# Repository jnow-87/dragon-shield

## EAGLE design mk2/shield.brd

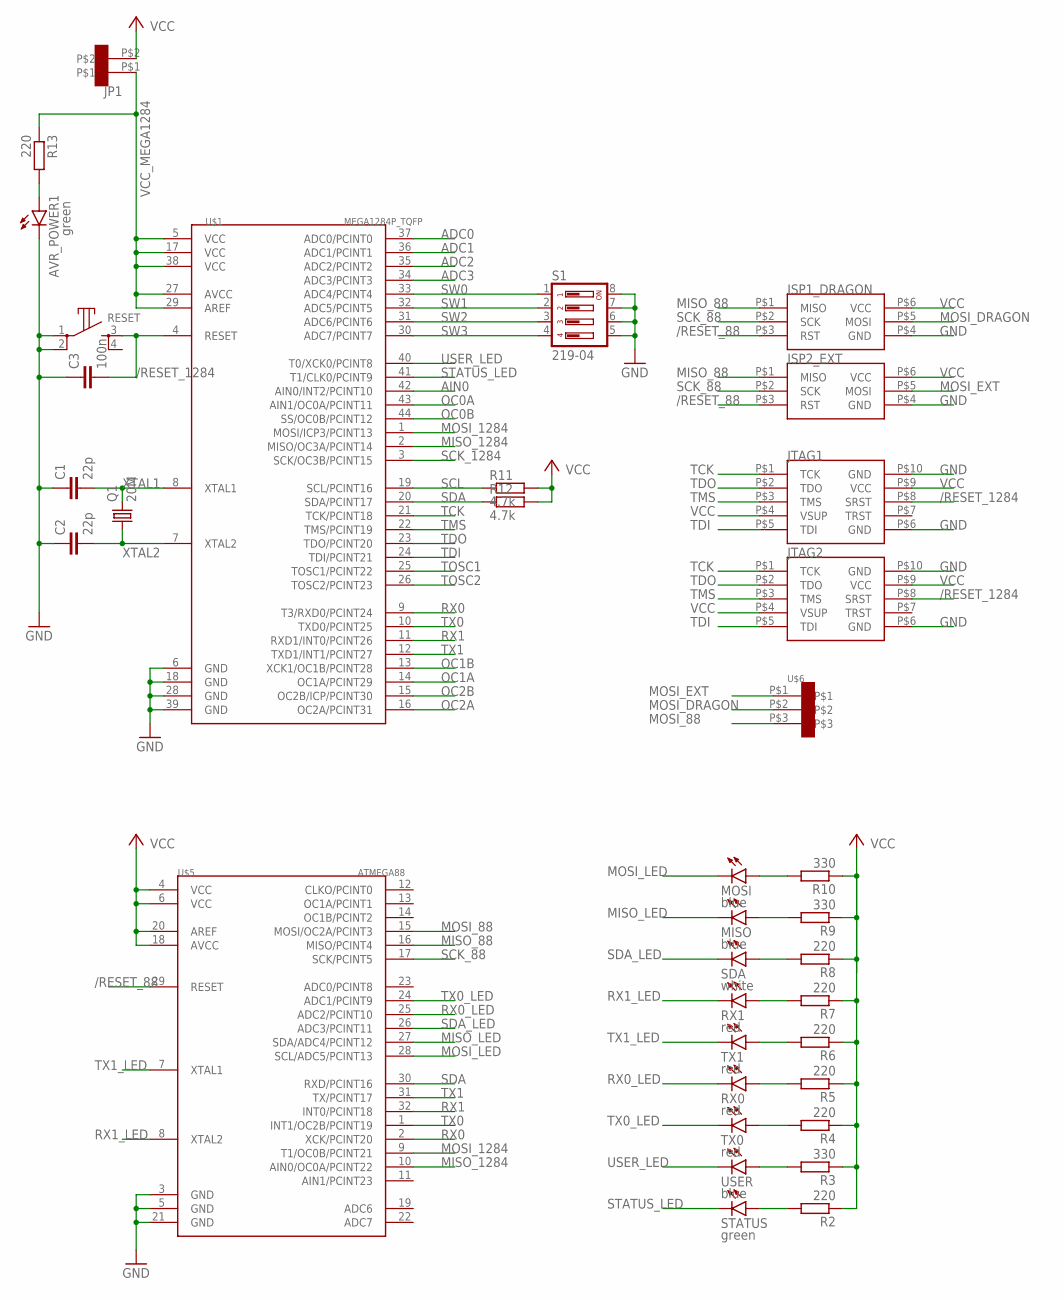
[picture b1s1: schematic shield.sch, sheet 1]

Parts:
AVR_POWER1: green; CHIP-LED0603
C1, C2: 22p; C0603
C3: 100n; C0603
ISP1_DRAGON, ISP2_EXT: ISP; CON_DIL_2X3
JP1: CON_DIL_2
JTAG1, JTAG2: JTAG; CON_DIL_2X5
MISO: blue; CHIP-LED0603
MOSI: blue; CHIP-LED0603
Q1: 20M; HC49U-V
R2, R4, R5, R6, R7, R8, R13: 220; R0603
R3, R9, R10: 330; R0603
R11, R12: 4.7k; R0603
RESET: 4-1437565-2; B3S-10XX
RX0, RX1: red; CHIP-LED0603
S1: 219-04; CTS-219-04
SDA: white; CHIP-LED0603
STATUS: green; CHIP-LED0603
TX0, TX1: red; CHIP-LED0603
U$1: MEGA1284P_TQFP; TQFP44
U$5: ATMEGA88; TQFP32-08
U$6: CON_DIL_3
USER: blue; CHIP-LED0603

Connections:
/RESET_88: ISP1_DRAGON.P$3 (RST), ISP2_EXT.P$3 (RST), U$5.29 (RESET)
/RESET_1284: C3.2, JTAG1.P$8 (SRST), JTAG2.P$8 (SRST), RESET.3, U$1.4 (RESET); also elsewhere on the board
ADC0: U$1.37 (ADC0/PCINT0); also elsewhere on the board
ADC1: U$1.36 (ADC1/PCINT1); also elsewhere on the board
ADC2: U$1.35 (ADC2/PCINT2); also elsewhere on the board
ADC3: U$1.34 (ADC3/PCINT3); also elsewhere on the board
AIN0: U$1.42 (AIN0/INT2/PCINT10); also elsewhere on the board
GND: AVR_POWER1.C, C1.1, C2.1, C3.1, ISP1_DRAGON.P$4 (GND), ISP2_EXT.P$4 (GND), JTAG1.P$6 (GND), JTAG1.P$10 (GND), JTAG2.P$6 (GND), JTAG2.P$10 (GND), RESET.1, RESET.2, S1.5, S1.6, S1.7, S1.8, U$1.6 (GND), U$1.18 (GND), U$1.28 (GND), U$1.39 (GND), U$5.3 (GND), U$5.5 (GND), U$5.21 (GND); also elsewhere on the board
MISO_88: ISP1_DRAGON.P$1 (MISO), ISP2_EXT.P$1 (MISO), U$5.16 (MISO/PCINT4)
MISO_1284: U$1.2 (MISO/OC3A/PCINT14), U$5.10 (AIN0/OC0A/PCINT22); also elsewhere on the board
MISO_LED: MISO.C, U$5.27 (SDA/ADC4/PCINT12)
MOSI_88: U$5.15 (MOSI/OC2A/PCINT3), U$6.P$3
MOSI_1284: U$1.1 (MOSI/ICP3/PCINT13), U$5.9 (T1/OC0B/PCINT21); also elsewhere on the board
MOSI_DRAGON: ISP1_DRAGON.P$5 (MOSI), U$6.P$2
MOSI_EXT: ISP2_EXT.P$5 (MOSI), U$6.P$1
MOSI_LED: MOSI.C, U$5.28 (SCL/ADC5/PCINT13)
unnamed: R2.2, STATUS.A
unnamed: R4.2, TX0.A
unnamed: R5.2, RX0.A
unnamed: R6.2, TX1.A
unnamed: R7.2, RX1.A
unnamed: R8.2, SDA.A
unnamed: R3.2, USER.A
unnamed: MISO.A, R9.2
unnamed: MOSI.A, R10.2
unnamed: AVR_POWER1.A, R13.2
OC0A: U$1.43 (AIN1/OC0A/PCINT11); also elsewhere on the board
OC0B: U$1.44 (SS/OC0B/PCINT12); also elsewhere on the board
OC1A: U$1.14 (OC1A/PCINT29); also elsewhere on the board
OC1B: U$1.13 (XCK1/OC1B/PCINT28); also elsewhere on the board
OC2A: U$1.16 (OC2A/PCINT31); also elsewhere on the board
OC2B: U$1.15 (OC2B/ICP/PCINT30); also elsewhere on the board
RX0: U$1.9 (T3/RXD0/PCINT24), U$5.2 (XCK/PCINT20); also elsewhere on the board
RX0_LED: RX0.C, U$5.25 (ADC2/PCINT10)
RX1: U$1.11 (RXD1/INT0/PCINT26), U$5.32 (INT0/PCINT18); also elsewhere on the board
RX1_LED: RX1.C, U$5.8 (XTAL2)
SCK_88: ISP1_DRAGON.P$2 (SCK), ISP2_EXT.P$2 (SCK), U$5.17 (SCK/PCINT5)
SCK_1284: U$1.3 (SCK/OC3B/PCINT15); also elsewhere on the board
SCL: R11.1, U$1.19 (SCL/PCINT16); also elsewhere on the board
SDA: R12.1, U$1.20 (SDA/PCINT17), U$5.30 (RXD/PCINT16); also elsewhere on the board
SDA_LED: SDA.C, U$5.26 (ADC3/PCINT11)
STATUS_LED: STATUS.C, U$1.41 (T1/CLK0/PCINT9); also elsewhere on the board
SW0: S1.1, U$1.33 (ADC4/PCINT4); also elsewhere on the board
SW1: S1.2, U$1.32 (ADC5/PCINT5); also elsewhere on the board
SW2: S1.3, U$1.31 (ADC6/PCINT6); also elsewhere on the board
SW3: S1.4, U$1.30 (ADC7/PCINT7); also elsewhere on the board
TCK: JTAG1.P$1 (TCK), JTAG2.P$1 (TCK), U$1.21 (TCK/PCINT18); also elsewhere on the board
TDI: JTAG1.P$5 (TDI), JTAG2.P$5 (TDI), U$1.24 (TDI/PCINT21); also elsewhere on the board
TDO: JTAG1.P$2 (TDO), JTAG2.P$2 (TDO), U$1.23 (TDO/PCINT20); also elsewhere on the board
TMS: JTAG1.P$3 (TMS), JTAG2.P$3 (TMS), U$1.22 (TMS/PCINT19); also elsewhere on the board
TOSC1: U$1.25 (TOSC1/PCINT22); also elsewhere on the board
TOSC2: U$1.26 (TOSC2/PCINT23); also elsewhere on the board
TX0: U$1.10 (TXD0/PCINT25), U$5.1 (INT1/OC2B/PCINT19); also elsewhere on the board
TX0_LED: TX0.C, U$5.24 (ADC1/PCINT9)
TX1: U$1.12 (TXD1/INT1/PCINT27), U$5.31 (TX/PCINT17); also elsewhere on the board
TX1_LED: TX1.C, U$5.7 (XTAL1)
USER_LED: U$1.40 (T0/XCK0/PCINT8), USER.C; also elsewhere on the board
VCC: ISP1_DRAGON.P$6 (VCC), ISP2_EXT.P$6 (VCC), JP1.P$2, JTAG1.P$4 (VSUP), JTAG1.P$9 (VCC), JTAG2.P$4 (VSUP), JTAG2.P$9 (VCC), R2.1, R3.1, R4.1, R5.1, R6.1, R7.1, R8.1, R9.1, R10.1, R11.2, R12.2, U$5.4 (VCC), U$5.6 (VCC), U$5.18 (AVCC), U$5.20 (AREF); also elsewhere on the board
VCC_MEGA1284: JP1.P$1, R13.1, U$1.5 (VCC), U$1.17 (VCC), U$1.27 (AVCC), U$1.29 (AREF), U$1.38 (VCC); also elsewhere on the board
XTAL1: C1.2, Q1.2, U$1.8 (XTAL1); also elsewhere on the board
XTAL2: C2.2, Q1.1, U$1.7 (XTAL2); also elsewhere on the board

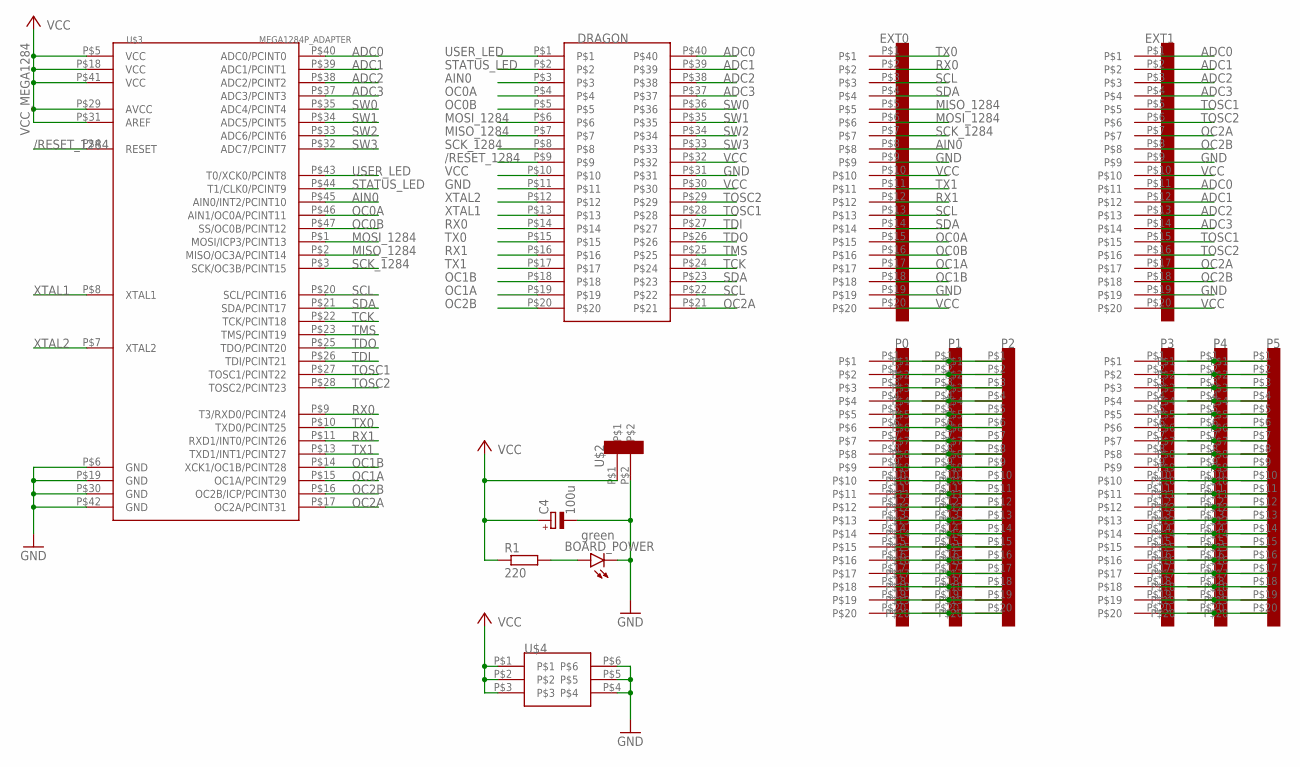
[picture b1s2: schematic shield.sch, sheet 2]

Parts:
BOARD_POWER: green; CHIP-LED0603
C4: 100u; E2,5-5
DRAGON: CON_DIL_2X20
EXT0, EXT1: CON_DIL_20
P0, P1, P2, P3, P4, P5: CON_DIL_20
R1: 220; R0603
U$2: CON_DIL_2
U$3: MEGA1284P_ADAPTER; TQFP44-ADAPTER
U$4: CON_DIL_2X3

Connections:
/RESET_1284: DRAGON.P$9, U$3.P$4 (RESET); also elsewhere on the board
ADC0: DRAGON.P$40, EXT1.P$1, EXT1.P$11, U$3.P$40 (ADC0/PCINT0); also elsewhere on the board
ADC1: DRAGON.P$39, EXT1.P$2, EXT1.P$12, U$3.P$39 (ADC1/PCINT1); also elsewhere on the board
ADC2: DRAGON.P$38, EXT1.P$3, EXT1.P$13, U$3.P$38 (ADC2/PCINT2); also elsewhere on the board
ADC3: DRAGON.P$37, EXT1.P$4, EXT1.P$14, U$3.P$37 (ADC3/PCINT3); also elsewhere on the board
AIN0: DRAGON.P$3, EXT0.P$8, U$3.P$45 (AIN0/INT2/PCINT10); also elsewhere on the board
GND: BOARD_POWER.C, C4.-, DRAGON.P$11, DRAGON.P$31, EXT0.P$9, EXT0.P$19, EXT1.P$9, EXT1.P$19, U$2.P$2, U$3.P$6 (GND), U$3.P$19 (GND), U$3.P$30 (GND), U$3.P$42 (GND), U$4.P$4, U$4.P$5, U$4.P$6; also elsewhere on the board
MISO_1284: DRAGON.P$7, EXT0.P$5, U$3.P$2 (MISO/OC3A/PCINT14); also elsewhere on the board
MOSI_1284: DRAGON.P$6, EXT0.P$6, U$3.P$1 (MOSI/ICP3/PCINT13); also elsewhere on the board
unnamed: BOARD_POWER.A, R1.2
unnamed: P0.P$1, P1.P$1, P2.P$1
unnamed: P0.P$2, P1.P$2, P2.P$2
unnamed: P0.P$3, P1.P$3, P2.P$3
unnamed: P0.P$4, P1.P$4, P2.P$4
unnamed: P0.P$5, P1.P$5, P2.P$5
unnamed: P0.P$6, P1.P$6, P2.P$6
unnamed: P0.P$7, P1.P$7, P2.P$7
unnamed: P0.P$8, P1.P$8, P2.P$8
unnamed: P0.P$9, P1.P$9, P2.P$9
unnamed: P0.P$10, P1.P$10, P2.P$10
unnamed: P0.P$11, P1.P$11, P2.P$11
unnamed: P0.P$12, P1.P$12, P2.P$12
unnamed: P0.P$13, P1.P$13, P2.P$13
unnamed: P0.P$14, P1.P$14, P2.P$14
unnamed: P0.P$15, P1.P$15, P2.P$15
unnamed: P0.P$16, P1.P$16, P2.P$16
unnamed: P0.P$17, P1.P$17, P2.P$17
unnamed: P0.P$18, P1.P$18, P2.P$18
unnamed: P0.P$19, P1.P$19, P2.P$19
unnamed: P0.P$20, P1.P$20, P2.P$20
unnamed: P3.P$1, P4.P$1, P5.P$1
unnamed: P3.P$2, P4.P$2, P5.P$2
unnamed: P3.P$3, P4.P$3, P5.P$3
unnamed: P3.P$4, P4.P$4, P5.P$4
unnamed: P3.P$5, P4.P$5, P5.P$5
unnamed: P3.P$6, P4.P$6, P5.P$6
unnamed: P3.P$7, P4.P$7, P5.P$7
unnamed: P3.P$8, P4.P$8, P5.P$8
unnamed: P3.P$9, P4.P$9, P5.P$9
unnamed: P3.P$10, P4.P$10, P5.P$10
unnamed: P3.P$11, P4.P$11, P5.P$11
unnamed: P3.P$12, P4.P$12, P5.P$12
unnamed: P3.P$13, P4.P$13, P5.P$13
unnamed: P3.P$14, P4.P$14, P5.P$14
unnamed: P3.P$15, P4.P$15, P5.P$15
unnamed: P3.P$16, P4.P$16, P5.P$16
unnamed: P3.P$17, P4.P$17, P5.P$17
unnamed: P3.P$18, P4.P$18, P5.P$18
unnamed: P3.P$19, P4.P$19, P5.P$19
unnamed: P3.P$20, P4.P$20, P5.P$20
OC0A: DRAGON.P$4, EXT0.P$15, U$3.P$46 (AIN1/OC0A/PCINT11); also elsewhere on the board
OC0B: DRAGON.P$5, EXT0.P$16, U$3.P$47 (SS/OC0B/PCINT12); also elsewhere on the board
OC1A: DRAGON.P$19, EXT0.P$17, U$3.P$15 (OC1A/PCINT29); also elsewhere on the board
OC1B: DRAGON.P$18, EXT0.P$18, U$3.P$14 (XCK1/OC1B/PCINT28); also elsewhere on the board
OC2A: DRAGON.P$21, EXT1.P$7, EXT1.P$17, U$3.P$17 (OC2A/PCINT31); also elsewhere on the board
OC2B: DRAGON.P$20, EXT1.P$8, EXT1.P$18, U$3.P$16 (OC2B/ICP/PCINT30); also elsewhere on the board
RX0: DRAGON.P$14, EXT0.P$2, U$3.P$9 (T3/RXD0/PCINT24); also elsewhere on the board
RX1: DRAGON.P$16, EXT0.P$12, U$3.P$11 (RXD1/INT0/PCINT26); also elsewhere on the board
SCK_1284: DRAGON.P$8, EXT0.P$7, U$3.P$3 (SCK/OC3B/PCINT15); also elsewhere on the board
SCL: DRAGON.P$22, EXT0.P$3, EXT0.P$13, U$3.P$20 (SCL/PCINT16); also elsewhere on the board
SDA: DRAGON.P$23, EXT0.P$4, EXT0.P$14, U$3.P$21 (SDA/PCINT17); also elsewhere on the board
STATUS_LED: DRAGON.P$2, U$3.P$44 (T1/CLK0/PCINT9); also elsewhere on the board
SW0: DRAGON.P$36, U$3.P$35 (ADC4/PCINT4); also elsewhere on the board
SW1: DRAGON.P$35, U$3.P$34 (ADC5/PCINT5); also elsewhere on the board
SW2: DRAGON.P$34, U$3.P$33 (ADC6/PCINT6); also elsewhere on the board
SW3: DRAGON.P$33, U$3.P$32 (ADC7/PCINT7); also elsewhere on the board
TCK: DRAGON.P$24, U$3.P$22 (TCK/PCINT18); also elsewhere on the board
TDI: DRAGON.P$27, U$3.P$26 (TDI/PCINT21); also elsewhere on the board
TDO: DRAGON.P$26, U$3.P$25 (TDO/PCINT20); also elsewhere on the board
TMS: DRAGON.P$25, U$3.P$23 (TMS/PCINT19); also elsewhere on the board
TOSC1: DRAGON.P$28, EXT1.P$5, EXT1.P$15, U$3.P$27 (TOSC1/PCINT22); also elsewhere on the board
TOSC2: DRAGON.P$29, EXT1.P$6, EXT1.P$16, U$3.P$28 (TOSC2/PCINT23); also elsewhere on the board
TX0: DRAGON.P$15, EXT0.P$1, U$3.P$10 (TXD0/PCINT25); also elsewhere on the board
TX1: DRAGON.P$17, EXT0.P$11, U$3.P$13 (TXD1/INT1/PCINT27); also elsewhere on the board
USER_LED: DRAGON.P$1, U$3.P$43 (T0/XCK0/PCINT8); also elsewhere on the board
VCC: C4.+, DRAGON.P$10, DRAGON.P$30, DRAGON.P$32, EXT0.P$10, EXT0.P$20, EXT1.P$10, EXT1.P$20, R1.1, U$2.P$1, U$4.P$1, U$4.P$2, U$4.P$3; also elsewhere on the board
VCC_MEGA1284: U$3.P$5 (VCC), U$3.P$18 (VCC), U$3.P$29 (AVCC), U$3.P$31 (AREF), U$3.P$41 (VCC); also elsewhere on the board
XTAL1: DRAGON.P$13, U$3.P$8 (XTAL1); also elsewhere on the board
XTAL2: DRAGON.P$12, U$3.P$7 (XTAL2); also elsewhere on the board

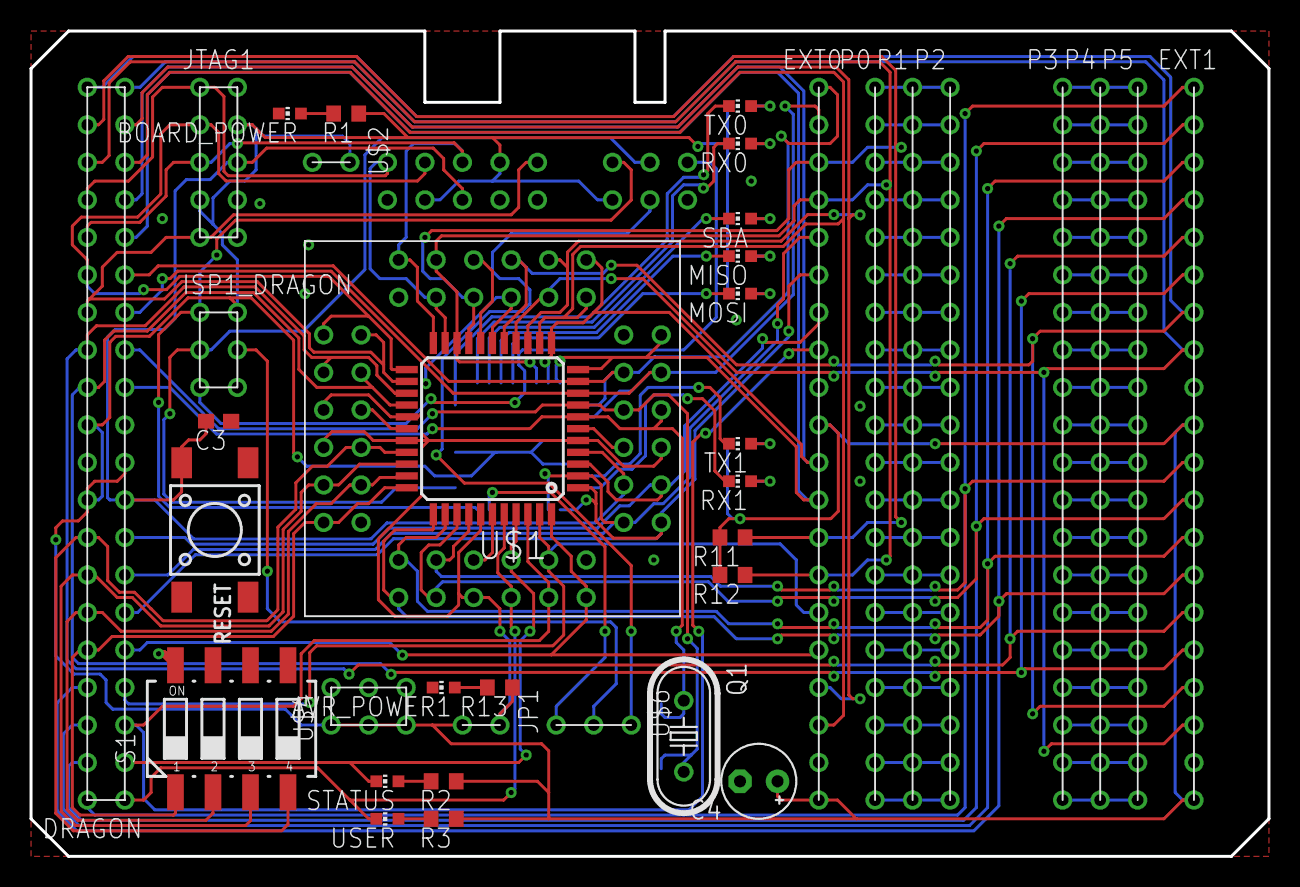
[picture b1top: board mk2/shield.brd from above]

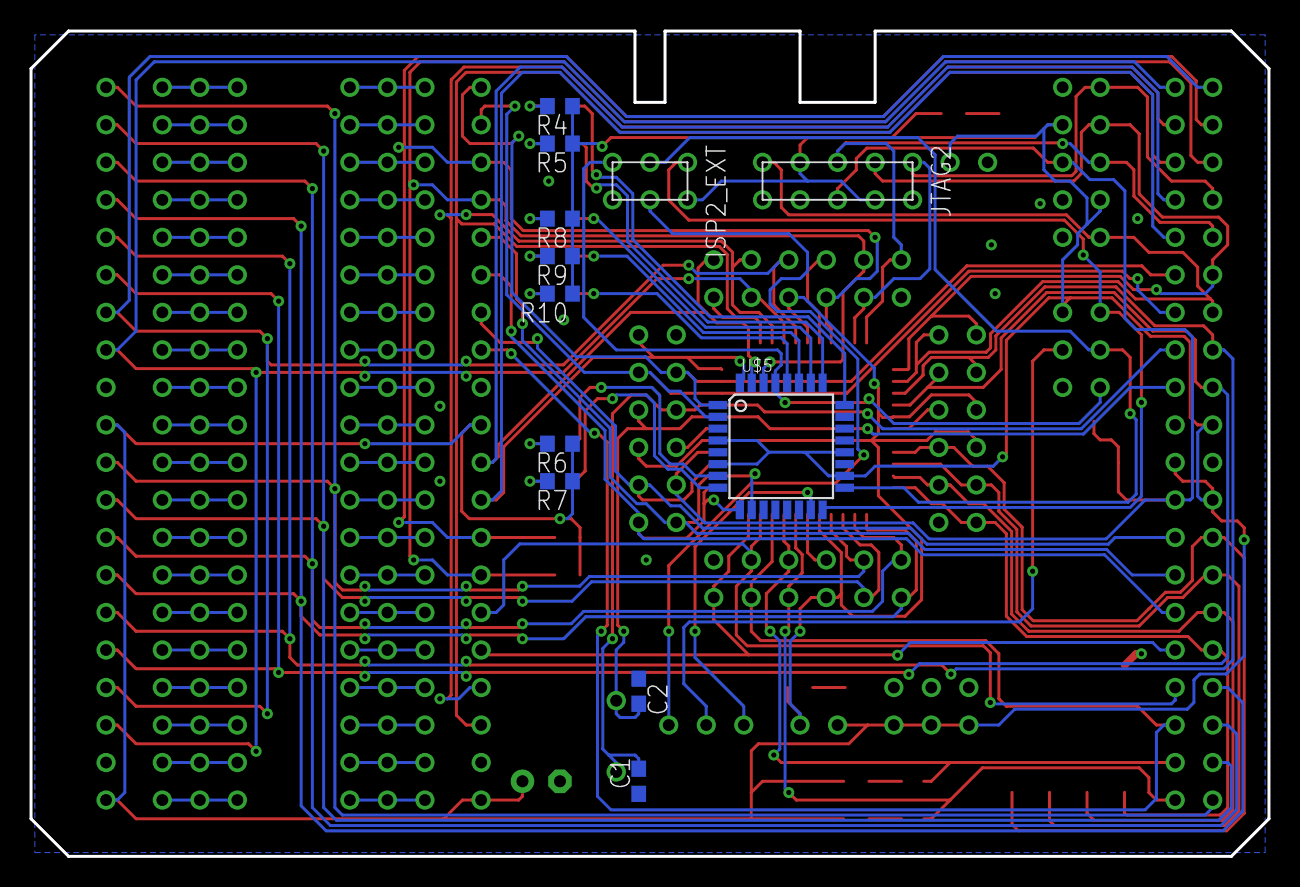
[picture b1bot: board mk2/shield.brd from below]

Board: 2 copper layers, 83.8 x 55.9 mm, 51 parts (12 on the bottom side), 102 nets.

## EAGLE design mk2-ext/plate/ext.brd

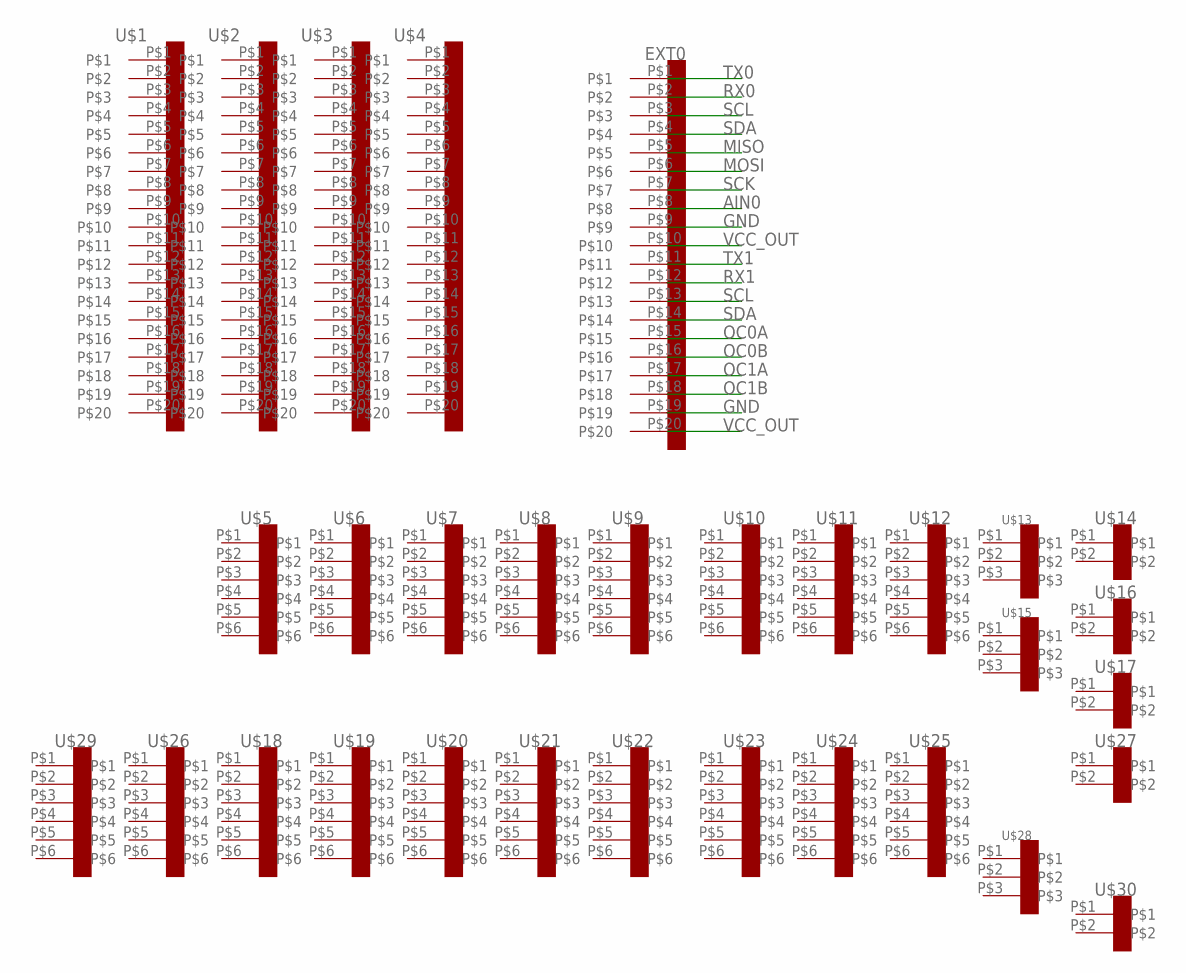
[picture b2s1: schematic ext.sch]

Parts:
EXT0: CON_DIL_20
U$1, U$2, U$3, U$4: CON_DIL_20
U$5, U$6, U$7, U$8, U$9, U$10, U$11, U$12, U$18, U$19, U$20, U$21, U$22, U$23, U$24, U$25, U$26, U$29: CON_DIL_6
U$13, U$15, U$28: CON_DIL_3
U$14, U$16, U$17, U$27, U$30: CON_DIL_2

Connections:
AIN0: EXT0.P$8
GND: EXT0.P$9, EXT0.P$19
MISO: EXT0.P$5
MOSI: EXT0.P$6
OC0A: EXT0.P$15
OC0B: EXT0.P$16
OC1A: EXT0.P$17
OC1B: EXT0.P$18
RX0: EXT0.P$2
RX1: EXT0.P$12
SCK: EXT0.P$7
SCL: EXT0.P$3, EXT0.P$13
SDA: EXT0.P$4, EXT0.P$14
TX0: EXT0.P$1
TX1: EXT0.P$11
VCC_OUT: EXT0.P$10, EXT0.P$20

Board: 2 copper layers, 31 parts (0 on the bottom side), 4 nets, no tracks yet.

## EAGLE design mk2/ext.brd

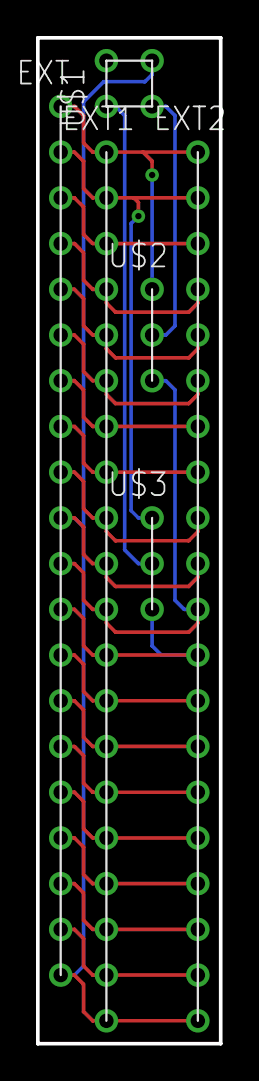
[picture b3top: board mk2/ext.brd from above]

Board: 2 copper layers, 10.2 x 55.9 mm, 6 parts (0 on the bottom side), 20 nets.

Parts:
EXT, EXT1, EXT2: CON_DIL_20
U$1: CON_DIL_2X2
U$2, U$3: CON_DIL_3

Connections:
EXT_AIN0: EXT.P$8, EXT1.P$8, EXT2.P$8
EXT_MISO: EXT.P$5, EXT1.P$5, EXT2.P$5
EXT_MOSI: EXT.P$6, EXT1.P$6, EXT2.P$6
EXT_OC0A: EXT.P$15, EXT1.P$15, EXT2.P$15
EXT_OC0B: EXT.P$16, EXT1.P$16, EXT2.P$16
EXT_OC1A: EXT.P$17, EXT1.P$17, EXT2.P$17
EXT_OC1B: EXT.P$18, EXT1.P$18, EXT2.P$18
EXT_RX0: EXT.P$2, EXT1.P$2, EXT2.P$2, U$3.P$1
EXT_RX1: EXT.P$12, EXT1.P$12, EXT2.P$12, U$3.P$3
EXT_SCK: EXT.P$7, EXT1.P$7, EXT2.P$7
EXT_SCL0: EXT.P$3, EXT1.P$3, EXT2.P$3
EXT_SCL1: EXT.P$13, EXT1.P$13, EXT2.P$13
EXT_SDA0: EXT.P$4, EXT1.P$4, EXT2.P$4
EXT_SDA1: EXT.P$14, EXT1.P$14, EXT2.P$14
EXT_TX0: EXT.P$1, EXT1.P$1, EXT2.P$1, U$2.P$1
EXT_TX1: EXT.P$11, EXT1.P$11, EXT2.P$11, U$2.P$3
GND: EXT.P$9, EXT.P$19, EXT1.P$9, EXT1.P$19, EXT2.P$9, EXT2.P$19, U$1.P$3
RX: U$1.P$1, U$3.P$2
TX: U$1.P$2, U$2.P$2
VCC: EXT.P$10, EXT.P$20, EXT1.P$10, EXT1.P$20, EXT2.P$10, EXT2.P$20, U$1.P$4

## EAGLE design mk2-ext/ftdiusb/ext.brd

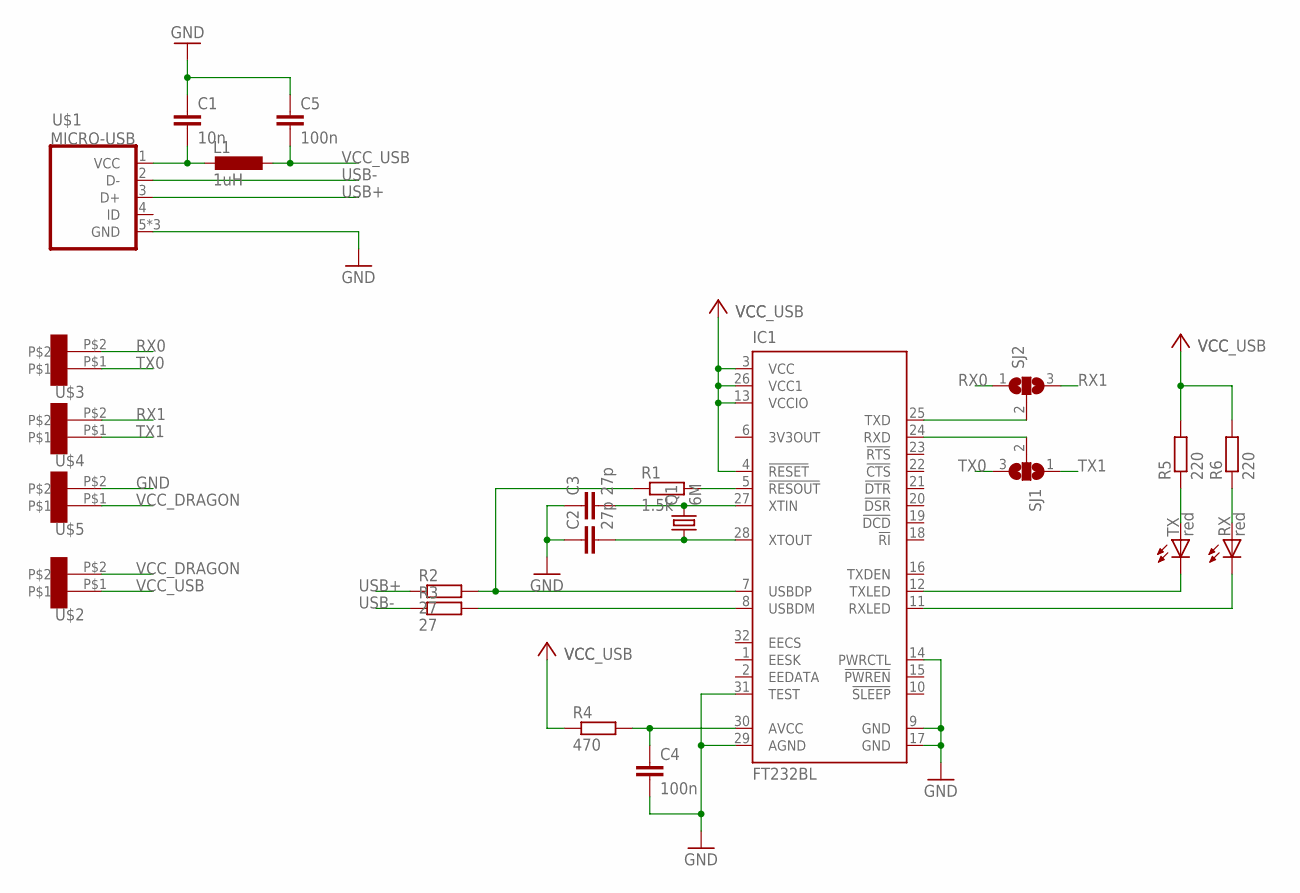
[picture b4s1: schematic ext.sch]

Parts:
C1: 10n; C0603
C2, C3: 27p; C0603
C4, C5: 100n; C0603
IC1: FT232BL; LQFP32-7X7
L1: 1uH; L0603
Q1: 6M; HC49U-V
R1: 1.5k; R0603
R2, R3: 27; R0603
R4: 470; R0603
R5, R6: 220; R0603
RX: red; C0603
SJ1, SJ2: SJ2WW; SJ_2W
TX: red; C0603
U$1: MICRO-USB
U$2, U$3, U$4, U$5: CON_DIL_2

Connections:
GND: C1.1, C2.1, C3.1, C4.2, C5.1, IC1.9 (GND), IC1.14 (PWRCTL), IC1.17 (GND), IC1.29 (AGND), IC1.31 (TEST), U$1.5 (GND), U$1.GND1 (GND), U$1.GND2 (GND), U$5.P$2
unnamed: IC1.5 (!RESOUT), R1.2
unnamed: IC1.7 (USBDP), R1.1, R2.2
unnamed: IC1.8 (USBDM), R3.2
unnamed: C1.2, L1.2, U$1.1 (VCC)
unnamed: IC1.25 (TXD), SJ2.2
unnamed: C3.2, IC1.27 (XTIN), Q1.2
unnamed: C2.2, IC1.28 (XTOUT), Q1.1
unnamed: IC1.24 (RXD), SJ1.2
unnamed: IC1.12 (TXLED), TX.N
unnamed: R5.1, TX.P
unnamed: C4.1, IC1.30 (AVCC), R4.2
unnamed: R6.1, RX.P
unnamed: IC1.11 (RXLED), RX.N
RX0: SJ2.1, U$3.P$2
RX1: SJ2.3, U$4.P$2
TX0: SJ1.3, U$3.P$1
TX1: SJ1.1, U$4.P$1
USB+: R2.1, U$1.3 (D+)
USB-: R3.1, U$1.2 (D-)
VCC_DRAGON: U$2.P$2, U$5.P$1
VCC_USB: C5.2, IC1.3 (VCC), IC1.4 (!RESET), IC1.13 (VCCIO), IC1.26 (VCC1), L1.1, R4.1, R5.2, R6.2, U$2.P$1

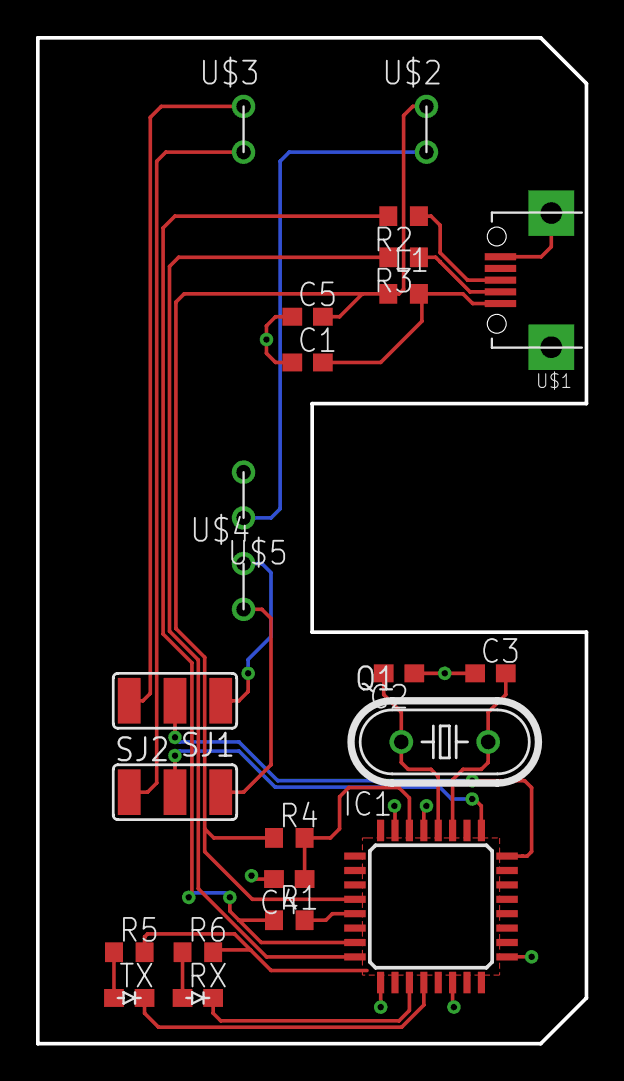
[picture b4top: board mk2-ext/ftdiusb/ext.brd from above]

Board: 2 copper layers, 30.5 x 55.9 mm, 23 parts (0 on the bottom side), 22 nets.

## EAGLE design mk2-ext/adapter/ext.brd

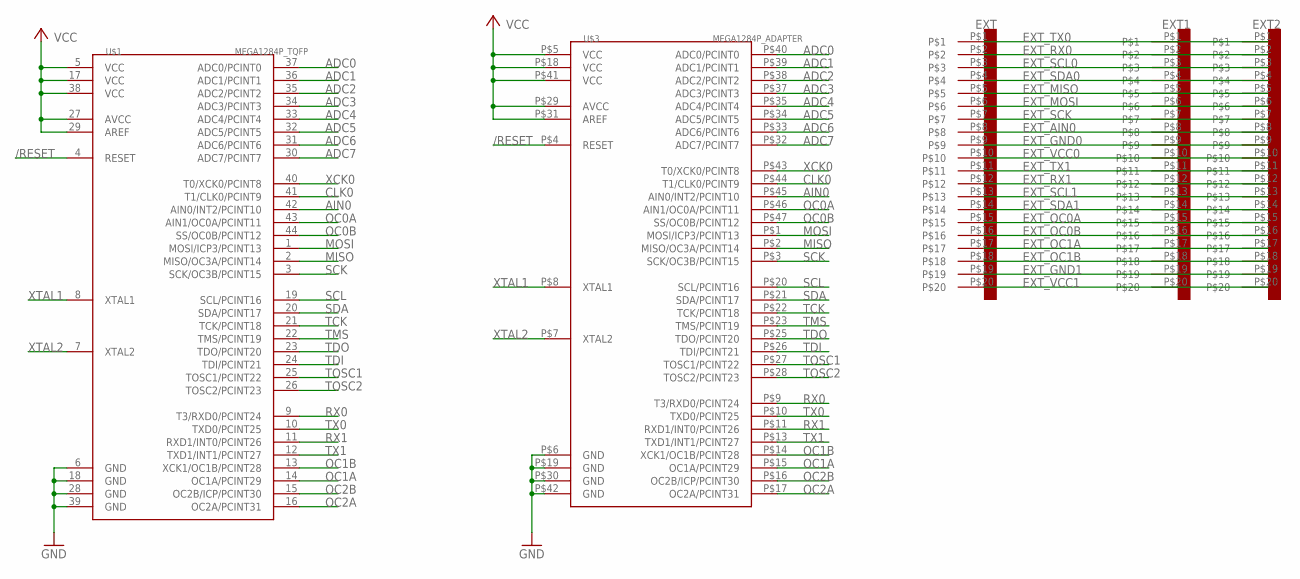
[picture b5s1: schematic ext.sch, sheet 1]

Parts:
EXT, EXT1, EXT2: CON_DIL_20
U$1: MEGA1284P_TQFP; TQFP44
U$3: MEGA1284P_ADAPTER; TQFP44-ADAPTER

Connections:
/RESET: U$1.4 (RESET), U$3.P$4 (RESET)
ADC0: U$1.37 (ADC0/PCINT0), U$3.P$40 (ADC0/PCINT0)
ADC1: U$1.36 (ADC1/PCINT1), U$3.P$39 (ADC1/PCINT1)
ADC2: U$1.35 (ADC2/PCINT2), U$3.P$38 (ADC2/PCINT2)
ADC3: U$1.34 (ADC3/PCINT3), U$3.P$37 (ADC3/PCINT3)
ADC4: U$1.33 (ADC4/PCINT4), U$3.P$35 (ADC4/PCINT4)
ADC5: U$1.32 (ADC5/PCINT5), U$3.P$34 (ADC5/PCINT5)
ADC6: U$1.31 (ADC6/PCINT6), U$3.P$33 (ADC6/PCINT6)
ADC7: U$1.30 (ADC7/PCINT7), U$3.P$32 (ADC7/PCINT7)
AIN0: U$1.42 (AIN0/INT2/PCINT10), U$3.P$45 (AIN0/INT2/PCINT10)
CLK0: U$1.41 (T1/CLK0/PCINT9), U$3.P$44 (T1/CLK0/PCINT9)
EXT_AIN0: EXT.P$8, EXT1.P$8, EXT2.P$8
EXT_GND0: EXT.P$9, EXT1.P$9, EXT2.P$9
EXT_GND1: EXT.P$19, EXT1.P$19, EXT2.P$19
EXT_MISO: EXT.P$5, EXT1.P$5, EXT2.P$5
EXT_MOSI: EXT.P$6, EXT1.P$6, EXT2.P$6
EXT_OC0A: EXT.P$15, EXT1.P$15, EXT2.P$15
EXT_OC0B: EXT.P$16, EXT1.P$16, EXT2.P$16
EXT_OC1A: EXT.P$17, EXT1.P$17, EXT2.P$17
EXT_OC1B: EXT.P$18, EXT1.P$18, EXT2.P$18
EXT_RX0: EXT.P$2, EXT1.P$2, EXT2.P$2
EXT_RX1: EXT.P$12, EXT1.P$12, EXT2.P$12
EXT_SCK: EXT.P$7, EXT1.P$7, EXT2.P$7
EXT_SCL0: EXT.P$3, EXT1.P$3, EXT2.P$3
EXT_SCL1: EXT.P$13, EXT1.P$13, EXT2.P$13
EXT_SDA0: EXT.P$4, EXT1.P$4, EXT2.P$4
EXT_SDA1: EXT.P$14, EXT1.P$14, EXT2.P$14
EXT_TX0: EXT.P$1, EXT1.P$1, EXT2.P$1
EXT_TX1: EXT.P$11, EXT1.P$11, EXT2.P$11
EXT_VCC0: EXT.P$10, EXT1.P$10, EXT2.P$10
EXT_VCC1: EXT.P$20, EXT1.P$20, EXT2.P$20
GND: U$1.6 (GND), U$1.18 (GND), U$1.28 (GND), U$1.39 (GND), U$3.P$6 (GND), U$3.P$19 (GND), U$3.P$30 (GND), U$3.P$42 (GND)
MISO: U$1.2 (MISO/OC3A/PCINT14), U$3.P$2 (MISO/OC3A/PCINT14)
MOSI: U$1.1 (MOSI/ICP3/PCINT13), U$3.P$1 (MOSI/ICP3/PCINT13)
OC0A: U$1.43 (AIN1/OC0A/PCINT11), U$3.P$46 (AIN1/OC0A/PCINT11)
OC0B: U$1.44 (SS/OC0B/PCINT12), U$3.P$47 (SS/OC0B/PCINT12)
OC1A: U$1.14 (OC1A/PCINT29), U$3.P$15 (OC1A/PCINT29)
OC1B: U$1.13 (XCK1/OC1B/PCINT28), U$3.P$14 (XCK1/OC1B/PCINT28)
OC2A: U$1.16 (OC2A/PCINT31), U$3.P$17 (OC2A/PCINT31)
OC2B: U$1.15 (OC2B/ICP/PCINT30), U$3.P$16 (OC2B/ICP/PCINT30)
RX0: U$1.9 (T3/RXD0/PCINT24), U$3.P$9 (T3/RXD0/PCINT24)
RX1: U$1.11 (RXD1/INT0/PCINT26), U$3.P$11 (RXD1/INT0/PCINT26)
SCK: U$1.3 (SCK/OC3B/PCINT15), U$3.P$3 (SCK/OC3B/PCINT15)
SCL: U$1.19 (SCL/PCINT16), U$3.P$20 (SCL/PCINT16)
SDA: U$1.20 (SDA/PCINT17), U$3.P$21 (SDA/PCINT17)
TCK: U$1.21 (TCK/PCINT18), U$3.P$22 (TCK/PCINT18)
TDI: U$1.24 (TDI/PCINT21), U$3.P$26 (TDI/PCINT21)
TDO: U$1.23 (TDO/PCINT20), U$3.P$25 (TDO/PCINT20)
TMS: U$1.22 (TMS/PCINT19), U$3.P$23 (TMS/PCINT19)
TOSC1: U$1.25 (TOSC1/PCINT22), U$3.P$27 (TOSC1/PCINT22)
TOSC2: U$1.26 (TOSC2/PCINT23), U$3.P$28 (TOSC2/PCINT23)
TX0: U$1.10 (TXD0/PCINT25), U$3.P$10 (TXD0/PCINT25)
TX1: U$1.12 (TXD1/INT1/PCINT27), U$3.P$13 (TXD1/INT1/PCINT27)
VCC: U$1.5 (VCC), U$1.17 (VCC), U$1.27 (AVCC), U$1.29 (AREF), U$1.38 (VCC), U$3.P$5 (VCC), U$3.P$18 (VCC), U$3.P$29 (AVCC), U$3.P$31 (AREF), U$3.P$41 (VCC)
XCK0: U$1.40 (T0/XCK0/PCINT8), U$3.P$43 (T0/XCK0/PCINT8)
XTAL1: U$1.8 (XTAL1), U$3.P$8 (XTAL1)
XTAL2: U$1.7 (XTAL2), U$3.P$7 (XTAL2)

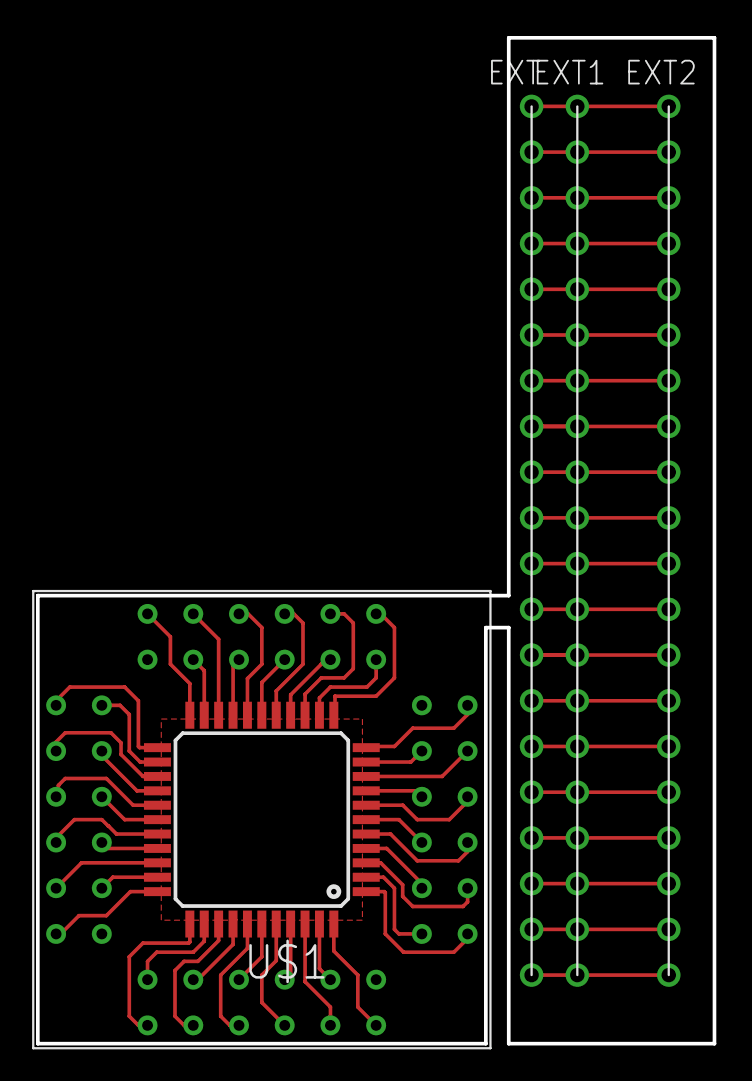
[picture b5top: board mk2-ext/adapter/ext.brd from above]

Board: 2 copper layers, 37.6 x 55.9 mm, 5 parts (0 on the bottom side), 57 nets.

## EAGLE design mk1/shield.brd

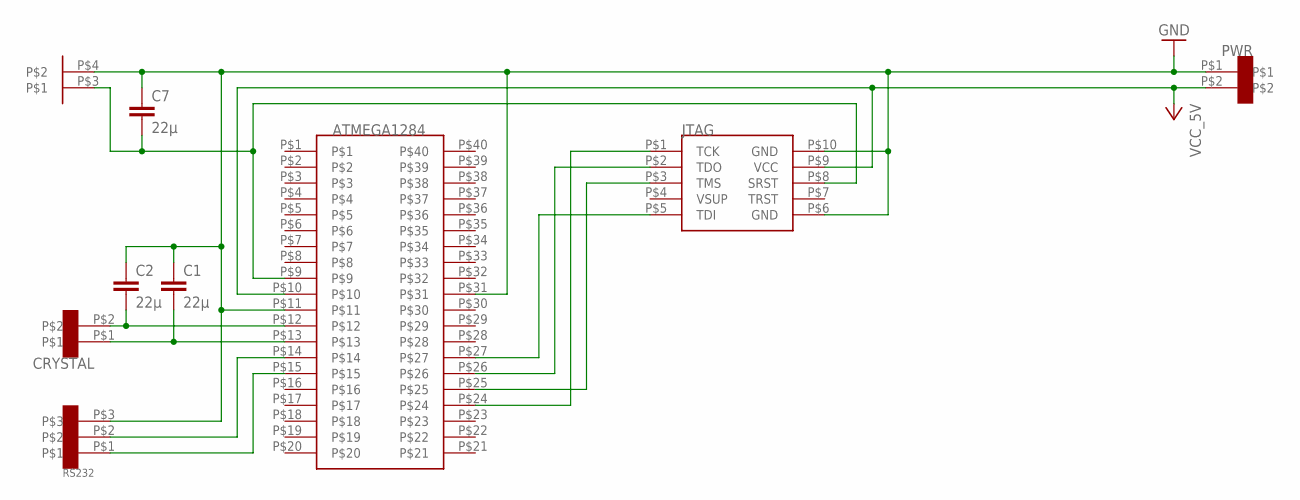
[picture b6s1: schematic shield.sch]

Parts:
ATMEGA1284: CON_DIL_2X20
C1, C2, C7: 22µ; C025-030X050
CRYSTAL: CON_DIL_2
JTAG: JTAG; CON_DIL_2X5
PWR: CON_DIL_2
RS232: CON_DIL_3
RST: RST

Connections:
GND: ATMEGA1284.P$11, ATMEGA1284.P$31, C1.1, C2.1, C7.1, JTAG.P$6 (GND), JTAG.P$10 (GND), PWR.P$1, RS232.P$3, RST.P$4
unnamed: ATMEGA1284.P$24, JTAG.P$1 (TCK)
unnamed: ATMEGA1284.P$25, JTAG.P$3 (TMS)
unnamed: ATMEGA1284.P$26, JTAG.P$2 (TDO)
unnamed: ATMEGA1284.P$27, JTAG.P$5 (TDI)
unnamed: ATMEGA1284.P$14, RS232.P$2
unnamed: ATMEGA1284.P$15, RS232.P$1
unnamed: ATMEGA1284.P$12, C2.2, CRYSTAL.P$2
unnamed: ATMEGA1284.P$13, C1.2, CRYSTAL.P$1
RST: ATMEGA1284.P$9, C7.2, JTAG.P$8 (SRST), RST.P$3
VCC: ATMEGA1284.P$10, JTAG.P$9 (VCC), PWR.P$2

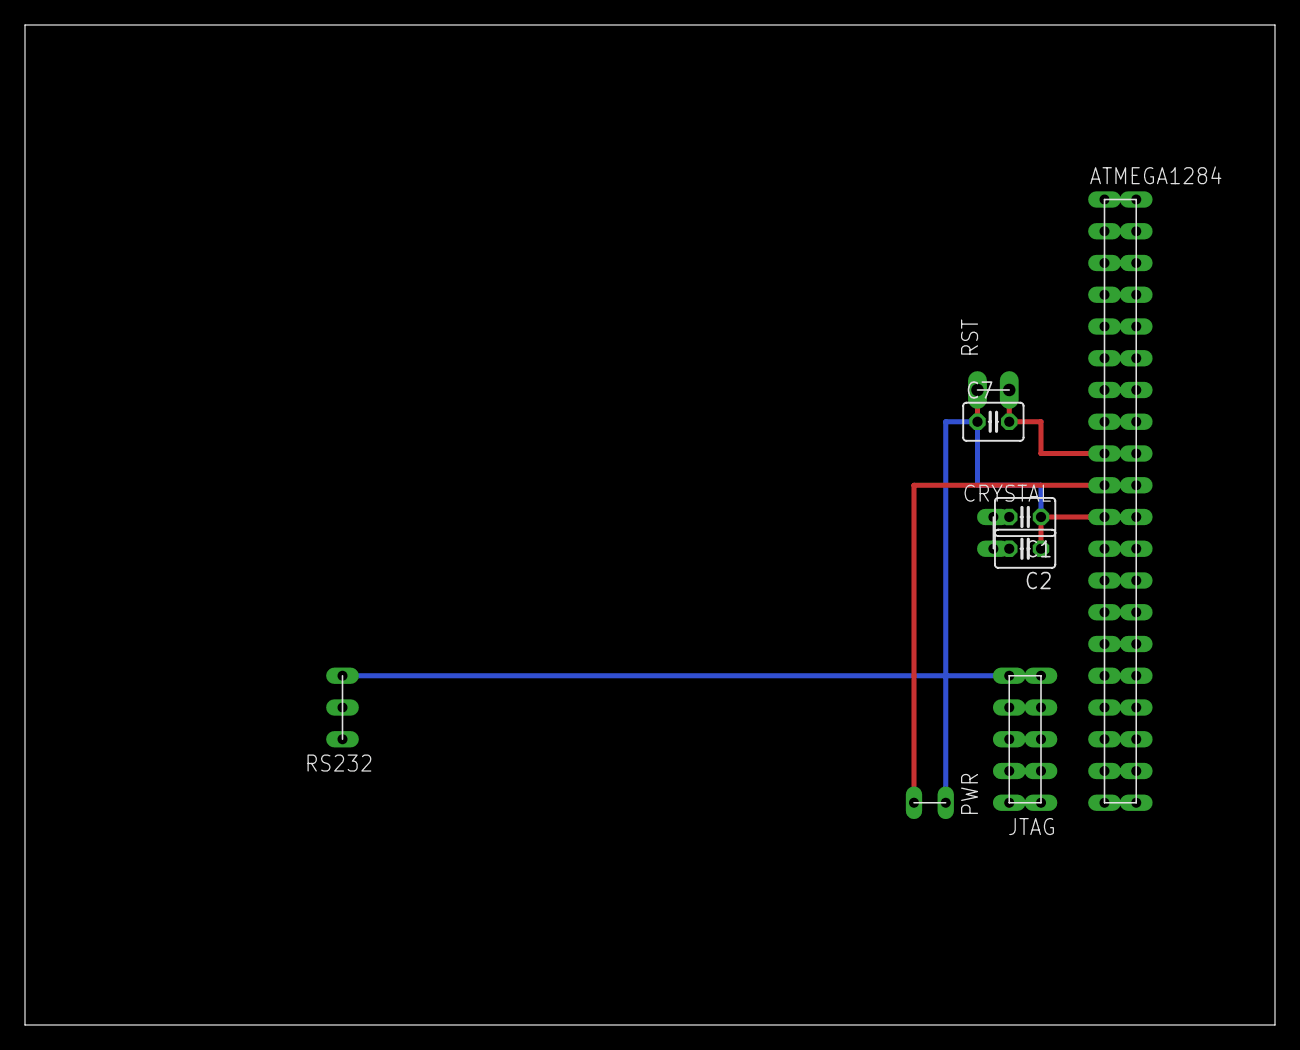
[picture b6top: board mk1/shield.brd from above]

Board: 2 copper layers, 100.0 x 80.0 mm, 9 parts (0 on the bottom side), 11 nets.

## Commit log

2020-05-25 [mk1]
    - add initial version of mk1
2020-05-30 [mk2]
    - add initial version of the mk2 shield
2020-06-05 [mega88 led ctrl]
    - add atmega88 controller for interface leds
2020-06-06 [relocate]
    - make more space on the right side of the board to increase the
    size of extension boards
2020-06-06 [ftdi usb adapter]
    - add ftdi usb adapter
2020-06-06 [mk2 adapter]
    - add mk2 extension adapter
    - add atmega1284 smd adapter
2020-06-16 [mk2 adapter split]
    - split the mk2-ext adapters into the actual mk2 extension board and
    the atmega1284 smd adapter
2020-06-16 [fix mk2 text size]
    - increase the font size of texts to make the smallest ones readable
    for the mk2 shield, extension header and ftdiusb extension board
2020-06-16 [mk2 update part values]
    - update/add values of some parts for mk2 shield and mk2 ftdiusb
    extension board
2020-06-16 [mk2 extension template]
    - add template schematic and board for mk2 extension boards
2020-06-16 [fix mk2 supply connector]
    - fix the position of the supply power connector since it didn't
    match the avr dragon header
2020-06-17 [fix atmega1284p adapter drill size]
    - extend the drill size of the atmega1284p adapter
2020-06-17 [update fonts]
    - change the size and font of board texts
2020-06-29 [ftdiusb sideways]
    - add a version of the ftdiusb board that is targeted towards the
    side of mk2 extension header board
    - rename the former ftdiusb board
2020-06-29 [fix mk2 power out connector]
    - move the power out connector as well as the avr power and the
    miso select headers to avoid overlap with the switches
2020-06-29 [fix mk2 power connector]
    - move the power connector to the dragon board to match the actual
    position on the dragon
2020-06-29 [mk2 extension uart]
    - add a uart header and tx/rx config header to the mk2.1 extension
2020-06-29 [mk2 reset separation]
    - split the jtag and isp connectors such that
    - isp is connected to the atmega88 and the external isp
    - jtat is connected to the atmega1284 and the external jtag
2020-06-29 [mk2 extension plate]
    - add an mk2 extension prototyping board
2020-06-29 [mk2 extension template dimensions]
    - increasing the size of the cutout needed for the avr dragon's
    usb-b port
2020-07-22 [initial atmega88 firmware]
    - add atmega88 firmware for controlling the dragon shield i/o leds
2020-07-22 Squashed 'firmware/scripts/build/' content from commit e1080be
    git-subtree-dir: firmware/scripts/build
    git-subtree-split: e1080be7eb0baaa9f1d3d7496b44ad0c24b19f54
2020-07-22 Squashed 'firmware/.githooks/' content from commit f2384fe
    git-subtree-dir: firmware/.githooks
    git-subtree-split: f2384fecb911fc3888e3a2d4a06c16e7cbc74db3
2020-07-22 [fix build system githooks target]
    issue:
    initialising githooks fails if the main makefile is not
    contained in the repository root directory
    reason:
    the githooks target assumes to be executed in the repository
    root directory
2020-07-22 [build system: init]
    - add makefiles
    - add project configuration
    - add .gitignore
2020-07-22 [pin test]
    - add pin test application
2020-07-25 [refactor application init]
    - move mcu-specific init into separate function
    - add watchdog init function and respective configuration options
    - move pin/port configuration into mcu-specific file
2020-07-25 [uart config option]
    - add uart config option
2020-07-25 [default configurations]
    - add default configurations for atmega88 and atmega1284p
2020-07-25 [support atmega1284p]
    - add atmega1284p init function and pin/port configuration
2020-07-25 [application config options]
    - add config options for the actual firmware as well as the test
2020-07-25 [startup animation config option]
    - make the firmware startup animation configurable
2023-06-18 [buildsys: fix typo]
    issue: uart driver is not built
    reason: typo on the uart CONFIG variable
    fix: fix the typo
